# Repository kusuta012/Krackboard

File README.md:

# Krackboard
**A RP2040 devboard**

This is my first big project , I have no prior experience with building electronic stuff , it was very fun to design this devboard.
I have followed  KaiPereira™ tutorial. 

# SCHEMATICS

# PCB 

# SHOWCASE

# JLCPCB 

# BOM

| LCSC Part Number | Description | Total Quantity | Ext. Price (USD) |
|------------------|-------------|----------------|----------------------|
| C25104 | 330Ω resistor 0402 | 2 | 0.0014 |
| C52923 | 1µF capacitor 0402 | 4 | 0.012 |
| C39051 | MCP1700T-3302 LDO | 5 | 1.7895 |
| C1562 | 33pF capacitor | 4 | 0.0044 |
| C11702 | 1kΩ resistor | 4 | 0.0024 |
| C25905 | 5.1kΩ resistor | 4 | 0.0024 |
| C9002 | 12 MHz crystal | 2 | 0.136 |
| C91447 | IRM-H638T IR receiver | 5 | 1.0965 |
| C19702 | 10µF capacitor | 4 | 0.024 |
| C25076 | 100Ω resistor | 2 | 0.0012 |
| C2040 | RP2040 MCU | 2 | 1.913 |
| C1525 | 0.1µF capacitor | 22 | 0.0286 |
| C2843335 | W25Q16JV Flash | 2 | 1.8284 |
| C25744 | 10kΩ resistor | 2 | 0.0012 |
| C165948 | USB-C Type-C-31-M-12 | 2 | 0.3538 |
| C25100 | 27Ω resistor | 20 | 0.012 |
| C720477 | SW_Push | 2 | 0.0890 |
| LOCAL_SHOP | WS2812B-2020 RGB LED | 1 | 0.15 |
| LOCAL_SHOP | Connector 1x20 | 2 | 0.33 |
| LOCAL_SHOP | Connector 1x03 | 1 | 0.1 |

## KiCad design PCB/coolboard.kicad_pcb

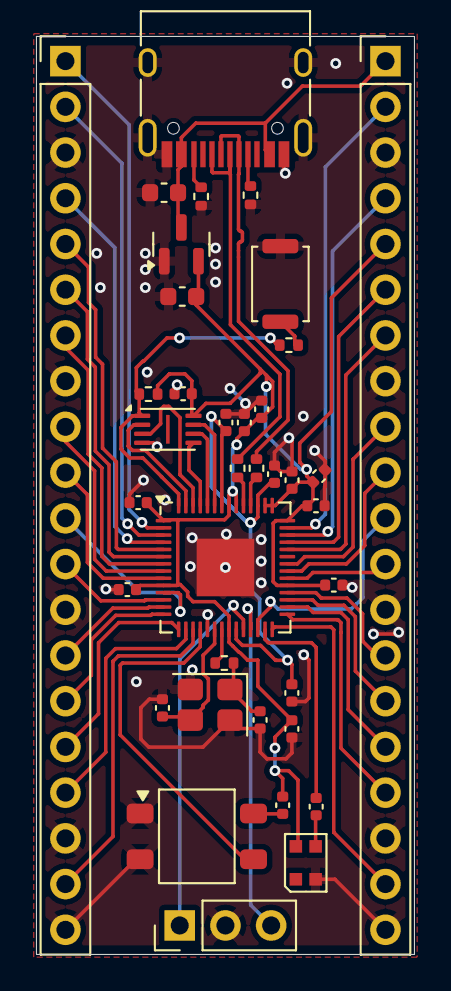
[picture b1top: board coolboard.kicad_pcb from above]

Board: 2 copper layers, 21.0 x 51.0 mm, 37 parts (0 on the bottom side), 54 nets.

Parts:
C1, C10: 1uF; C_0402_1005Metric
C2, C3, C4, C5, C6, C7, C8, C9, C11, C12, C17: 0.1uF; C_0402_1005Metric
C13, C14: 10uF; C_0603_1608Metric
C15, C16: 33pF; C_0402_1005Metric
D1: WS2812B-2020; LED_WS2812B-2020_PLCC4_2.0x2.0mm
J1: USB_C_Receptacle_USB2.0_14P; USB_C_Receptacle_HRO_TYPE-C-31-M-12
J2, J3: Conn_01x20; PinHeader_1x20_P2.54mm_Vertical
J4: Conn_01x03; PinHeader_1x03_P2.54mm_Vertical
R1, R2: 5.1K; R_0402_1005Metric
R3, R4: 27; R_0402_1005Metric
R5, R6: 1K; R_0402_1005Metric
R7: 10K; R_0402_1005Metric
R8: 330; C_0402_1005Metric
R9: 100; C_0402_1005Metric
SW1: SW_Push; SW_Push_SPST_NO_Alps_SKRK
U1: RP2040; QFN-56-1EP_7x7mm_P0.4mm_EP3.2x3.2mm
U2: MCP1700x-330xxTT; SOT-23
U3: IRM-H6xxT; Everlight_IRM-H6xxT
U4: W25Q16JVUXIQ TR; Winbond_USON-8-1EP_3x2mm_P0.5mm_EP0.2x1.6mm
Y1: 12 MHz; Crystal_SMD_3225-4Pin_3.2x2.5mm

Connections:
+1V1: C10.1, C11.1, C12.1, U1.23 (DVDD), U1.45 (VREG_VOUT), U1.50 (DVDD)
+3V3: C1.1, C2.1, C3.1, C4.1, C5.1, C6.1, C7.1, C8.1, C9.1, C14.1, C17.1, D1.4 (VDD), J3.5, R7.2, R9.2, U1.1 (IOVDD), U1.10 (IOVDD), U1.22 (IOVDD), U1.33 (IOVDD), U1.42 (IOVDD), U1.43 (ADC_AVDD), U1.44 (VREG_IN), U1.48 (USB_VDD), U1.49 (IOVDD), U2.2 (VO), U4.8 (VCC)
GND: C1.2, C2.2, C3.2, C4.2, C5.2, C6.2, C7.2, C8.2, C9.2, C10.2, C11.2, C12.2, C13.2, C14.2, C15.1, C16.1, C17.2, D1.2 (VSS), J1.A1 (GND), J1.A12 (GND), J1.B1 (GND), J1.B12 (GND), J1.S1 (SHIELD), J2.3, J2.8, J2.13, J2.18, J2.20, J3.3, J3.8, J3.13, J3.18, J3.20, J4.2, R1.2, R2.2, SW1.1, U1.19 (TESTEN), U1.57 (GND), U2.1 (GND), U3.1 (GND), U3.2 (GND), U4.4 (GND), Y1.2, Y1.4
GPIO0: J2.1, U1.2 (GPIO0)
GPIO1: J2.2, U1.3 (GPIO1)
GPIO2: J2.4, U1.4 (GPIO2)
GPIO3: J2.5, U1.5 (GPIO3)
GPIO4: J2.6, U1.6 (GPIO4)
GPIO5: J2.7, U1.7 (GPIO5)
GPIO6: J2.9, U1.8 (GPIO6)
GPIO7: J2.10, U1.9 (GPIO7)
GPIO8: J2.11, U1.11 (GPIO8)
GPIO9: J2.12, U1.12 (GPIO9)
GPIO10: J2.14, U1.13 (GPIO10)
GPIO11: J2.15, U1.14 (GPIO11)
GPIO12: J2.16, U1.15 (GPIO12)
GPIO13: J2.17, U1.16 (GPIO13)
GPIO14: J2.19, U1.17 (GPIO14)
GPIO15: U1.18 (GPIO15), U3.3 (OUT)
GPIO16: R8.1, U1.27 (GPIO16)
GPIO17: J3.19, U1.28 (GPIO17)
GPIO18: J3.17, U1.29 (GPIO18)
GPIO19: J3.16, U1.30 (GPIO19)
GPIO20: J3.15, U1.31 (GPIO20)
GPIO21: J3.14, U1.32 (GPIO21)
GPIO22: J3.12, U1.34 (GPIO22)
GPIO23: J3.10, U1.35 (GPIO23)
GPIO24: J3.9, U1.36 (GPIO24)
GPIO26_ADC0: J3.7, U1.38 (GPIO26_ADC0)
GPIO27_ADC1: J3.6, U1.39 (GPIO27_ADC1)
GPIO28_ADC2: J3.4, U1.40 (GPIO28_ADC2)
GPIO29_ADC3: J3.2, U1.41 (GPIO29_ADC3)
unnamed: C16.2, R5.1, Y1.1
unnamed: D1.3 (DIN), R8.2
unnamed: J1.A5 (CC1), R2.1
unnamed: J1.B5 (CC2), R1.1
unnamed: R6.2, SW1.2
unnamed: R4.2, U1.46 (USB_DM)
unnamed: R3.2, U1.47 (USB_DP)
unnamed: R9.1, U3.4 (Vcc)
QSPI_SCLK: U1.52 (QSPI_SCLK), U4.6 (CLK)
QSPI_SD0: U1.53 (QSPI_SD0), U4.5 (DI/IO_{0})
QSPI_SD1: U1.55 (QSPI_SD1), U4.2 (DO/IO_{1})
QSPI_SD2: U1.54 (QSPI_SD2), U4.3 (~WP/IO_{2})
QSPI_SD3: U1.51 (QSPI_SD3), U4.7 (~HOLD/~RESET/IO_{3})
QSPI_SS: R6.1, R7.1, U1.56 (QSPI_SS), U4.1 (~CS)
RUN: J3.11, U1.26 (RUN)
SWCLK: J4.1, U1.24 (SWCLK)
SWD: J4.3, U1.25 (SWD)
USB_D+: J1.A6 (D+), J1.B6 (D+), R3.1
USB_D-: J1.A7 (D-), J1.B7 (D-), R4.1
VBUS: C13.1, J1.A4 (VBUS), J1.A9 (VBUS), J1.B4 (VBUS), J1.B9 (VBUS), J3.1, U2.3 (VI)
XIN: C15.2, U1.20 (XIN), Y1.3
XOUT: R5.2, U1.21 (XOUT)

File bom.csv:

Comment,Designator,Footprint
IRM-H6xxT,U3,Everlight_IRM-H6xxT
100,R9,C_0402_1005Metric
0.1uF,"C8,C4,C11,C9,C2,C12,C5,C3,C7,C17,C6",C_0402_1005Metric
10uF,"C13,C14",C_0603_1608Metric
5.1K,"R2,R1",R_0402_1005Metric
27,"R4,R3",R_0402_1005Metric
10K,R7,R_0402_1005Metric
1uF,"C1,C10",C_0402_1005Metric
Conn_01x03,J4,PinHeader_1x03_P2.54mm_Vertical
USB_C_Receptacle_USB2.0_14P,J1,USB_C_Receptacle_HRO_TYPE-C-31-M-12
33pF,"C16,C15",C_0402_1005Metric
12 MHz,Y1,Crystal_SMD_3225-4Pin_3.2x2.5mm
WS2812B-2020,D1,LED_WS2812B-2020_PLCC4_2.0x2.0mm
W25Q16JVUXIQ TR,U4,Winbond_USON-8-1EP_3x2mm_P0.5mm_EP0.2x1.6mm
330,R8,C_0402_1005Metric
1K,"R6,R5",R_0402_1005Metric
RP2040,U1,QFN-56-1EP_7x7mm_P0.4mm_EP3.2x3.2mm
Conn_01x20,"J2,J3",PinHeader_1x20_P2.54mm_Vertical
MCP1700x-330xxTT,U2,SOT-23
SW_Push,SW1,SW_Push_SPST_NO_Alps_SKRK

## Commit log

2026-01-14 Added
2026-01-14 Enhance README with project details and images
    Added project description and images for schematics, PCB, and showcase.
2026-01-14 Add BOM section to README
    Added a Bill of Materials (BOM) section with component details.
2026-01-14 Update README with tutorial reference
    Added acknowledgment of KaiPereira™ tutorial.
2026-01-14 Add Cart section with image to README
    Added a new section for Cart with an image.
2026-01-15 Add new components to bom.csv
2026-01-15 Update production zip file with latest changes
2026-01-15 Replace old images with new screenshots in README
2026-01-15 Add JLCPCB section with images to README
2026-01-16 Remove cart section from README
    Removed cart section and associated image from README.
2026-01-23 Revise BOM with detailed part numbers and prices
    Updated BOM section with LCSC part numbers and pricing.
2026-01-23 Revise bom.csv to new format and add components
    Updated BOM file format and added new components with details.
2026-01-23 Replaced an image
2026-01-27 Correct resistor value from 270Ω to 27Ω
2026-01-27 Add SW_Push component to parts list
2026-01-27 Add new images to JLCPCB section in README
    Added two new images to the README section.
